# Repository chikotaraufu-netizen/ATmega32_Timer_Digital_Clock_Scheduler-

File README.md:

# ⏱️ ATmega32 Timer-Based Digital Clock & Task Scheduler

> A precision digital clock and cooperative task scheduler built on the ATmega32 microcontroller, leveraging Timer1 in CTC mode for accurate 1Hz timekeeping with USART-based HH:MM:SS display and multi-task LED scheduling.

---

## 📋 Table of Contents

- [Project Overview](#project-overview)
- [Features](#features)
- [System Architecture](#system-architecture)
- [Hardware Requirements](#hardware-requirements)
- [Software Requirements](#software-requirements)
- [Pin Mapping](#pin-mapping)
- [Build Instructions](#build-instructions)
- [Usage](#usage)
- [Repository Structure](#repository-structure)
- [Screenshots](#screenshots)
- [Documentation](#documentation)
- [License](#license)

---

## 🎯 Project Overview

This project implements a **real-time digital clock** and **cooperative task scheduler** on the **ATmega32** microcontroller running at **8 MHz** with an external crystal oscillator. The system uses **Timer1 in CTC (Clear Timer on Compare Match) mode** with a prescaler of 1024 and an OCR1A value of 7812 to generate a precise **1 Hz interrupt**—the heartbeat of the entire system.

The clock displays time in **HH:MM:SS** format via the **USART interface** at 9600 baud, while the task scheduler manages two LED tasks using a **non-blocking, ISR-flag-driven architecture**:

- **Status LED** (PB0): Toggles every **2 seconds**
- **Task LED** (PB1): Flashes every **5 seconds**

Three hardware buttons provide user interaction for time setting, field incrementing, and clock reset—all with internal pull-up resistors and active-low logic.

---

## ✨ Features

| Feature | Description |
|---------|-------------|
| **Precision Timekeeping** | Timer1 CTC mode with 1024 prescaler generates accurate 1Hz tick |
| **USART Display** | Real-time HH:MM:SS output at 9600 baud (8N1) |
| **Task Scheduler** | Cooperative, flag-based scheduler with configurable task intervals |
| **Status LED** | Heartbeat indicator toggling every 2 seconds |
| **Task LED** | Periodic flash every 5 seconds for task activity indication |
| **Time Set Mode** | Cycle through HH → MM → SS fields with SET button |
| **Increment Function** | Increment the currently selected time field |
| **Clock Reset** | Instantly reset time to 00:00:00 |
| **Non-Blocking Design** | ISR sets flags only; all processing happens in the main loop |
| **Low Power** | Efficient design suitable for battery-powered operation |

---

## 🏗️ System Architecture

The system follows a **flag-based cooperative scheduling** architecture where the Timer1 ISR sets scheduler flags, and the main loop polls and services those flags. This ensures deterministic behavior with minimal interrupt latency.

```mermaid
graph TB
    subgraph Hardware["🔧 Hardware Layer"]
        XTAL["8 MHz Crystal<br/>Oscillator"]
        MCU["ATmega32<br/>Microcontroller"]
        BTNS["Buttons<br/>SET | INC | RESET"]
        LEDS["LEDs<br/>Status | Task"]
        UART["USART<br/>TX/RX"]
    end

    subgraph Firmware["💻 Firmware Layer"]
        TIMER["Timer1 ISR<br/>CTC @ 1Hz"]
        SCHED["Task Scheduler<br/>Flag Polling"]
        CLOCK["Clock Module<br/>HH:MM:SS"]
        BTNDRV["Button Driver<br/>Debounce + Read"]
        LEDDRV["LED Driver<br/>Toggle/Flash"]
        UARTDRV["USART Driver<br/>9600 8N1"]
    end

    XTAL --> MCU
    MCU --> TIMER
    TIMER -->|"tick_flag"| SCHED
    SCHED --> CLOCK
    SCHED --> LEDDRV
    BTNS --> BTNDRV
    BTNDRV --> CLOCK
    CLOCK --> UARTDRV
    UARTDRV --> UART
    LEDDRV --> LEDS
```

### Architecture Principles

1. **ISR Minimalism**: The Timer1 Compare Match ISR only increments a counter and sets boolean flags—no heavy processing inside the ISR.
2. **Flag-Based Scheduling**: The main loop continuously polls scheduler flags and dispatches tasks when their flags are set.
3. **Separation of Concerns**: Clock logic, LED control, button handling, and USART communication are modular and independent.
4. **Non-Blocking I/O**: All operations are non-blocking to maintain responsive button handling and accurate timing.

---

## 🔌 Hardware Requirements

| Component | Specification | Quantity |
|-----------|--------------|----------|
| ATmega32 Microcontroller | PDIP-40 package (U1) | 1 |
| Crystal Oscillator | 8 MHz, HC49-U Vertical (Y1) | 1 |
| Load Capacitors | 22 pF ceramic (C3, C4) | 2 |
| Decoupling Capacitors | 100 nF ceramic (C1 VCC, C2 AVCC, C5 AREF) | 3 |
| LEDs | 5mm, any color (D1 Task, D2 Status) | 2 |
| LED Current Limiting Resistors | 220Ω, ¼W (R3, R5) | 2 |
| Button Pull-up Resistors | 10 kΩ (R1 Reset, R2 SET, R4 INC, R6 RESET_CLK) | 4 |
| Tactile Push Buttons | 6mm, normally open (SW1 Reset, SW2 SET, SW3 INC, SW4 CLOCK_RESET) | 4 |
| USART Connector | 1×3 pin header 2.54mm (J1: GND, TXD, RXD) | 1 |
| USB-to-UART Adapter | FTDI/CH340/CP2102 (3.3V/5V) | 1 |
| Breadboard or PCB | Standard breadboard or custom PCB | 1 |
| Power Supply | 5V DC regulated | 1 |
| Jumper Wires | Male-to-male, assorted | As needed |

### Schematic Overview

```
                        +----[VCC 5V]----+
                        |                |
                   [10kΩ]R1         [100nF]C1 (VCC decoupling)
                        |                |
          +----[SW1]----+---[RESET]------+---[GND]
          |
    +-----+-----+
    |  ATmega32  |
    |            |
    | PA0 (40)---+---[10kΩ R2]---[VCC]   [SW2 SET]---[GND]
    | PA1 (39)---+---[10kΩ R4]---[VCC]   [SW3 INC]---[GND]
    | PA2 (38)---+---[10kΩ R6]---[VCC]   [SW4 RST]---[GND]
    |            |
    | PB0 (1)----+---[220Ω R5]---[LED D2 STATUS]---[GND]
    | PB1 (2)----+---[220Ω R3]---[LED D1 TASK]-----[GND]
    |            |
    | PD0 (14)---+---[J1 Pin3 RXD]
    | PD1 (15)---+---[J1 Pin2 TXD]       J1 Pin1 = GND
    |            |
    | XTAL1(13)--+---[8MHz Y1]---+---[22pF C3]---[GND]
    | XTAL2(12)--+---[8MHz Y1]---+---[22pF C4]---[GND]
    |            |
    | VCC (10)---+---[5V]    [100nF C1]---[GND]
    | GND (11)---+---[GND]
    | AVCC(30)---+---[5V]    [100nF C2]---[GND]
    | AREF(32)---+---[100nF C5]---[GND]
    | GND (31)---+---[GND]
    +------------+
```

---

## 💻 Software Requirements

| Tool | Version | Purpose |
|------|---------|---------|
| **AVR-GCC** | ≥ 5.4.0 | C compiler for AVR targets |
| **AVR Libc** | ≥ 2.0.0 | Standard C library for AVR |
| **AVRDUDE** | ≥ 6.3 | Flash programmer utility |
| **GNU Make** | ≥ 4.0 | Build automation |
| **Serial Terminal** | PuTTY / minicom / screen | USART output viewing |

### Installation (Ubuntu/Debian)

```bash
sudo apt-get update
sudo apt-get install gcc-avr avr-libc avrdude make
```

### Installation (macOS with Homebrew)

```bash
brew tap osx-cross/avr
brew install avr-gcc avrdude
```

### Installation (Windows)

Download and install [WinAVR](http://winavr.sourceforge.net/) or use the [Microchip AVR Toolchain](https://www.microchip.com/en-us/tools-resources/develop/microchip-studio/gcc-compilers).

---

## 📌 Pin Mapping

| Pin # | Port/Pin | Function | Direction | Configuration | Description |
|-------|----------|----------|-----------|---------------|-------------|
| 40 | PA0 | SET_BTN | Input | External 10kΩ Pull-up (R2) | Enter time-set mode / cycle fields |
| 39 | PA1 | INC_BTN | Input | External 10kΩ Pull-up (R4) | Increment selected time field |
| 38 | PA2 | CLOCK_RESET | Input | External 10kΩ Pull-up (R6) | Reset clock to 00:00:00 |
| 1 | PB0 | LED_STATUS | Output | Active High, 220Ω (R5) | Status heartbeat LED (2s toggle) |
| 2 | PB1 | LED_TASK | Output | Active High, 220Ω (R3) | Task indicator LED (5s flash) |
| 9 | ~RESET | RESET | Input | External 10kΩ Pull-up (R1) | Hardware reset (SW1) |
| 10 | VCC | Power | — | +5V DC | Digital supply voltage |
| 11 | GND | Ground | — | 0V | Digital ground |
| 12 | XTAL2 | Crystal | — | 8 MHz + 22pF cap | Crystal oscillator output |
| 13 | XTAL1 | Crystal | — | 8 MHz + 22pF cap | Crystal oscillator input |
| 14 | PD0 | USART_RXD | Input | — | USART Receive Data |
| 15 | PD1 | USART_TXD | Output | — | USART Transmit Data |
| 30 | AVCC | Analog VCC | — | +5V DC | Analog supply voltage |
| 31 | AGND | Analog GND | — | 0V | Analog ground |

> 📖 For the complete 40-pin mapping, see [documentation/pin_mapping_table.md](documentation/pin_mapping_table.md)

---

## 🔨 Build Instructions

### 1. Clone the Repository

```bash
git clone https://github.com/yourusername/atmega32-digital-clock.git
cd atmega32-digital-clock
```

### 2. Configure the Makefile

Verify the following settings in `Makefile`:

```makefile
MCU       = atmega32
F_CPU     = 8000000UL
PROGRAMMER = usbasp
PORT      = usb
BAUD      = 9600
```

### 3. Compile the Project

```bash
make all
```

This will produce `main.hex` in the build directory.

### 4. Set Fuse Bits (First Time Only)

Configure the ATmega32 for an external 8 MHz crystal:

```bash
# Low Fuse:  0xFF (External Crystal, full swing, 16K CK + 64ms startup)
# High Fuse: 0xD9 (JTAG disabled, EEPROM preserved, Boot size 256 words)
avrdude -c usbasp -p m32 -U lfuse:w:0xFF:m -U hfuse:w:0xD9:m
```

> ⚠️ **Warning**: Incorrect fuse settings can brick your microcontroller. Double-check values before programming.

### 5. Flash the Firmware

```bash
make flash
# or manually:
avrdude -c usbasp -p m32 -U flash:w:main.hex:i
```

### 6. Connect Serial Terminal

```bash
# Linux
minicom -D /dev/ttyUSB0 -b 9600

# macOS
screen /dev/cu.usbserial-XXXX 9600

# Windows
# Use PuTTY with COM port at 9600 baud, 8N1
```

### 7. Verify Operation

After programming and connecting the serial terminal, you should see:

```
=====================================
  ATmega32 Digital Clock v1.0
  Timer1 CTC Mode | 8MHz Crystal
=====================================

TIME: 00:00:00
[500ms Tick] Ext Task
TIME: 00:00:01
[500ms Tick] Ext Task
TIME: 00:00:02
[500ms Tick] Ext Task
TIME: 00:00:03
[500ms Tick] Ext Task
TIME: 00:00:04
[500ms Tick] Ext Task
TIME: 00:00:05
TASK: SENSOR SAMPLE
[500ms Tick] Ext Task
...
```

---

## 🕹️ Usage

### Normal Operation

Upon power-up, the clock starts at **00:00:00** and counts up. Time is displayed on the serial terminal every second.

### Button Functions

| Button | Action | Behavior |
|--------|--------|----------|
| **SET** (PA0) | Press | Enters time-set mode. Successive presses cycle: **Hours → Minutes → Seconds → Exit** |
| **INCREMENT** (PA1) | Press | Increments the currently selected field (wraps: 23→0 for hours, 59→0 for min/sec) |
| **RESET** (PA2) | Press | Immediately resets the clock to **00:00:00** |

### LED Indicators

| LED | Port | Behavior |
|-----|------|----------|
| **Status LED** | PB0 | Toggles ON/OFF every **2 seconds** — heartbeat indicator |
| **Task LED** | PB1 | Brief flash every **5 seconds** — scheduled task indicator |

---

## 📁 Repository Structure

```
atmega32-digital-clock/
│
├── README.md                              # This file
├── LICENSE                                # MIT License
│
├── firmware/                              # Firmware source and hex
│   ├── src/                               # C Source files
│   │   ├── main.c                         # Main application entry
│   │   ├── timer.c                        # Timer config and ISR
│   │   ├── display.c                      # USART output logic
│   │   ├── scheduler.c                    # Non-blocking scheduler
│   │   └── buttons.c                      # Button debounce logic
│   ├── include/                           # Header files
│   │   ├── config.h                       # Pin definitions & constants
│   │   ├── timer.h
│   │   ├── display.h
│   │   ├── scheduler.h
│   │   └── buttons.h
│   ├── hex/
│   │   └── main.hex                       # Compiled firmware binary
│   └── Makefile                           # Build configuration
│
├── documentation/                         # Project documentation
│   ├── timer_configuration.md             # Timer1 CTC mode setup
│   ├── compare_match_calculation.md       # OCR1A calculation
│   ├── pin_mapping_table.md               # ATmega32 pin mapping
│   ├── test_results.md                    # Test plan and results
│   ├── block_diagram.md                   # System block diagram
│   └── flowchart.md                       # Program flowchart
│
├── simulide/                              # Simulation files
│   ├── circuit/                           # Simulide circuit docs
│   └── screenshots/                       # Simulation screenshots
│
└── kicad/                                 # Hardware design
    ├── schematic/                         # KiCad schematic
    ├── pcb/                               # KiCad PCB layout
    └── gerber/                            # Manufacturing files
```

---

## 📸 Screenshots

### SimulIDE Simulation Running

### KiCad PCB Layout

---

## 📚 Documentation

Detailed documentation is available in the `documentation/` directory:

| Document | Description |
|----------|-------------|
| [Timer Configuration](documentation/timer_configuration.md) | Detailed Timer1 CTC mode setup and register configuration |
| [Compare Match Calculation](documentation/compare_match_calculation.md) | Step-by-step OCR1A value derivation with accuracy analysis |
| [Pin Mapping Table](documentation/pin_mapping_table.md) | Complete ATmega32 PDIP-40 pin assignment reference |
| [Test Results](documentation/test_results.md) | Test plan, test cases, and verification results |
| [Block Diagram](documentation/block_diagram.md) | System architecture block diagram (Mermaid) |
| [Flowchart](documentation/flowchart.md) | Program flow and ISR logic flowchart (Mermaid) |

---

## 📄 License

This project is licensed under the **MIT License**.

```
MIT License

Copyright (c) 2026 ATmega32 Digital Clock Project

Permission is hereby granted, free of charge, to any person obtaining a copy
of this software and associated documentation files (the "Software"), to deal
in the Software without restriction, including without limitation the rights
to use, copy, modify, merge, publish, distribute, sublicense, and/or sell
copies of the Software, and to permit persons to whom the Software is
furnished to do so, subject to the following conditions:

The above copyright notice and this permission notice shall be included in all
copies or substantial portions of the Software.

THE SOFTWARE IS PROVIDED "AS IS", WITHOUT WARRANTY OF ANY KIND, EXPRESS OR
IMPLIED, INCLUDING BUT NOT LIMITED TO THE WARRANTIES OF MERCHANTABILITY,
FITNESS FOR A PARTICULAR PURPOSE AND NONINFRINGEMENT. IN NO EVENT SHALL THE
AUTHORS OR COPYRIGHT HOLDERS BE LIABLE FOR ANY CLAIM, DAMAGES OR OTHER
LIABILITY, WHETHER IN AN ACTION OF CONTRACT, TORT OR OTHERWISE, ARISING FROM,
OUT OF OR IN CONNECTION WITH THE SOFTWARE OR THE USE OR OTHER DEALINGS IN THE
SOFTWARE.
```

---

<p align="center">
  <b>Built with ❤️ for embedded systems enthusiasts</b><br>
  ATmega32 · Timer1 CTC · USART · Cooperative Scheduling
</p>

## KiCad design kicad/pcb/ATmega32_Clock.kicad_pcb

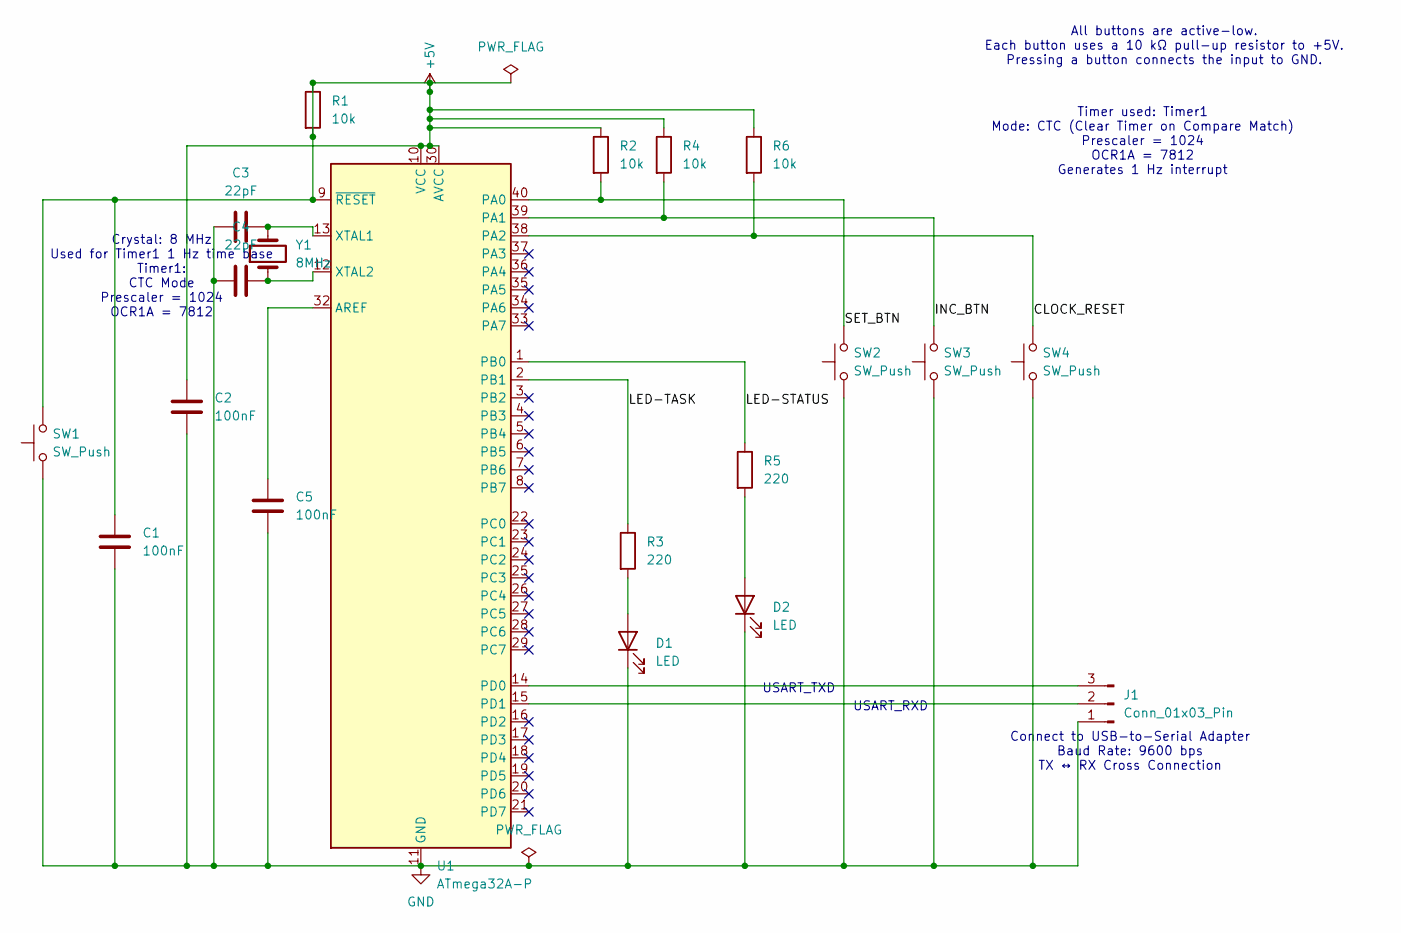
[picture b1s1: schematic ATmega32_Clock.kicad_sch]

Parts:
C1, C2, C5: 100nF; C_Disc_D5.0mm_W2.5mm_P5.00mm
C3, C4: 22pF; C_Disc_D5.0mm_W2.5mm_P5.00mm
D1, D2: LED; LED_D5.0mm
J1: Conn_01x03_Pin; PinHeader_1x03_P2.54mm_Vertical
R1, R2, R4, R6: 10k; R_Axial_DIN0207_L6.3mm_D2.5mm_P7.62mm_Horizontal
R3, R5: 220; R_Axial_DIN0207_L6.3mm_D2.5mm_P7.62mm_Horizontal
SW1, SW2, SW3, SW4: SW_Push; SW_PUSH_6mm
U1: ATmega32A-P; DIP-40_W15.24mm
Y1: 8MHz; Crystal_HC49-U_Vertical

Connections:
+5V: C1.1, C2.1, R1.1, R1.2, R2.1, R4.1, R6.1, SW1.2, U1.9 (~RESET), U1.10 (VCC), U1.30 (AVCC)
/CLOCK_RESET: R6.2, SW4.2, U1.38 (PA2)
/INC_BTN: R4.2, SW3.2, U1.39 (PA1)
/LED-STATUS: R5.1, U1.1 (PB0)
/LED-TASK: R3.1, U1.2 (PB1)
/SET_BTN: R2.2, SW2.2, U1.40 (PA0)
GND: C1.2, C2.2, C3.1, C4.1, C5.2, D1.1 (K), D2.1 (K), J1.1, SW1.1, SW2.1, SW3.1, SW4.1, U1.11 (GND), U1.31 (GND)
unnamed: D1.2 (A), R3.2
unnamed: D2.2 (A), R5.2
unnamed: J1.2, U1.15 (PD1)
unnamed: J1.3, U1.14 (PD0)
unnamed: C5.1, U1.32 (AREF)
unnamed: C3.2, U1.13 (XTAL1), Y1.2
unnamed: C4.2, U1.12 (XTAL2), Y1.1

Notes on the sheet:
All buttons are active-low. Each button uses a 10 kΩ pull-up resistor to +5V. Pressing a button connects the input to GND.
Crystal: 8 MHz Used for Timer1 1 Hz time base Timer1: CTC Mode Prescaler = 1024 OCR1A = 7812
Timer used: Timer1 Mode: CTC (Clear Timer on Compare Match) Prescaler = 1024 OCR1A = 7812 Generates 1 Hz interrupt
USART_RXD
Connect to USB-to-Serial Adapter Baud Rate: 9600 bps TX ↔ RX Cross Connection
USART_TXD

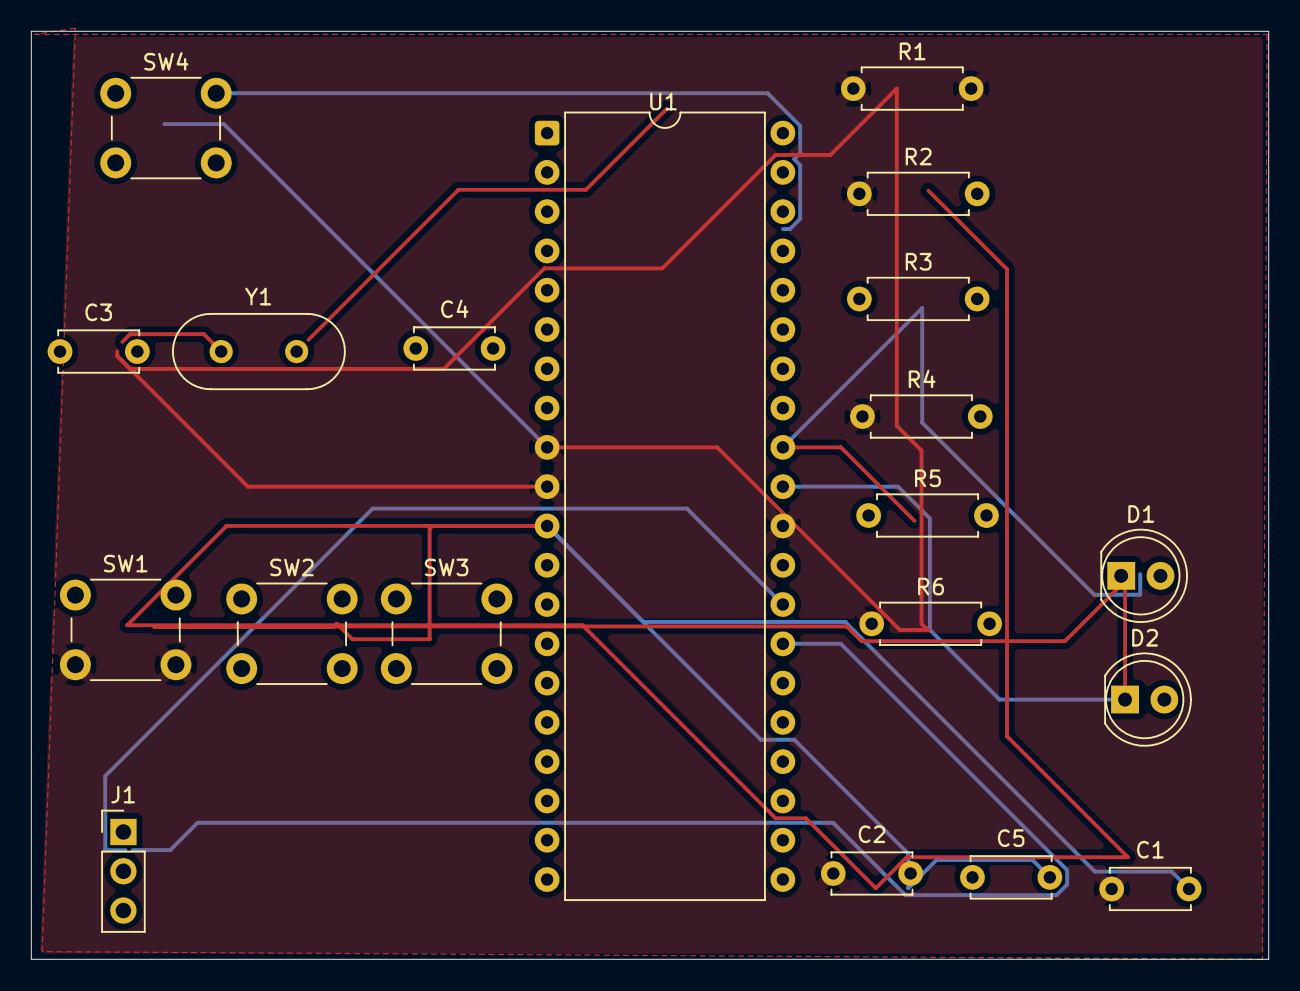
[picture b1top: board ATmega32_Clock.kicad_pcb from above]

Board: 2 copper layers, 80.0 x 60.0 mm, 20 parts (0 on the bottom side), 14 nets.

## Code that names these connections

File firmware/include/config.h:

/**
 * @file config.h
 * @brief Central configuration for ATmega32 Digital Clock & Task Scheduler
 *
 * All hardware-dependent constants, pin mappings, timer calculations,
 * and scheduler intervals are defined here for easy modification.
 *
 * Target MCU : ATmega32 (PDIP-40)
 * Clock      : 8 MHz external crystal
 */

#ifndef CONFIG_H
#define CONFIG_H

/* ========================== CPU Clock ================================== */
/**
 * F_CPU must be defined before including <util/delay.h> or any AVR header
 * that uses it.  8 MHz matches the external crystal on the target board.
 */
#ifndef F_CPU
#define F_CPU 8000000UL
#endif

/* ========================== Pin Mapping ================================ */
/*
 * PORTA – Buttons (active-low with internal pull-ups)
 *   PA0 (Pin 40) : SET_BTN      – Enter/cycle time-set mode
 *   PA1 (Pin 39) : INC_BTN      – Increment selected field
 *   PA2 (Pin 38) : CLOCK_RESET  – Reset clock to 00:00:00
 *
 * PORTB – LEDs (active-high outputs)
 *   PB0 (Pin 1)  : LED_STATUS   – Toggled every 2 s by scheduler
 *   PB1 (Pin 2)  : LED_TASK     – Brief flash every 5 s by scheduler
 *
 * PORTD – USART
 *   PD0 (Pin 14) : USART_RXD
 *   PD1 (Pin 15) : USART_TXD
 */

/* Button port/pins (PORTA) */
#define BTN_DDR     DDRA
#define BTN_PORT    PORTA
#define BTN_PIN     PINA
#define SET_BTN     PA0
#define INC_BTN     PA1
#define RESET_BTN   PA2

/* LED port/pins (PORTB) */
#define LED_DDR     DDRB
#define LED_PORT    PORTB
#define LED_STATUS  PB0
#define LED_TASK    PB1

/* ========================== Timer1 CTC Configuration =================== */
/**
 * Goal : generate a precise 1 Hz (1 s) interrupt from Timer1 in CTC mode.
 *
 * Calculation:
 *   f_OCR = F_CPU / (prescaler * (1 + OCR1A))
 *   1 Hz  = 8 000 000 / (1024 * (1 + OCR1A))
 *   1 + OCR1A = 8 000 000 / 1024 = 7812.5
 *   OCR1A = 7812  (yields ~1.000064 s period, negligible error)
 *
 * Prescaler bits: CS12=1, CS11=0, CS10=1  → clk/1024
 */
#define TIMER1_PRESCALER_BITS  ((1 << CS12) | (1 << CS10))
#define TIMER1_TOP             7812U

/* ========================== USART Configuration ======================== */
/**
 * Baud rate : 9600
 * UBRR = (F_CPU / (16 * BAUD)) - 1 = (8000000 / (16 * 9600)) - 1 = 51.08
 * Use 51 → actual baud ≈ 9615 (0.16 % error – well within tolerance).
 */
#define USART_BAUD       9600UL
#define USART_UBRR_VAL  ((F_CPU / (16UL * USART_BAUD)) - 1)

/* ========================== Scheduler Intervals ======================== */
/**
 * Intervals are expressed in ticks (Timer1 ISR ticks at 1 Hz / 1 s).
 */
#define SCHED_STATUS_LED_TICKS  2U    /* Toggle status LED every 2 ticks (2 s)   */
#define SCHED_TASK_LED_TICKS    5U    /* Flash task LED every 5 ticks (5 s)      */
#define SCHED_TASK_LED_ON_TICKS 1U    /* Task LED stays on for 1 tick (1 s)      */
#define SCHED_EXT_TASK_TICKS    10U   /* Extension task every 10 ticks (10 s)    */

/* ========================== Button Debounce ============================ */
/**
 * Debounce threshold in ticks.  At 1 Hz tick rate each tick is 1 second,
 * so a single stable reading is sufficient for debounce.
 */
#define DEBOUNCE_TICKS  1U

#endif /* CONFIG_H */

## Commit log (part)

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2026-06-15 Added Timer1 compare-match firmware
2026-06-15 Created timer scheduler project repository
2026-06-15 Added README and project media
2026-06-15 Added PCB layout and Gerber output instructions
2026-06-15 Added timer calculation and test documentation
2026-06-15 Added SimulIDE simulation circuit and screenshots guide
2026-06-15 Added KiCad schematic for timer project
2026-06-15 Generated KiCad 7 compatible Gerbers and Drill files via kicad-cli
2026-06-15 Implemented 10ms Timer1 Extension Task (100% score update)
2026-06-15 Added PNG diagrams
2026-06-15 Updated all documentation to reflect 10ms (100Hz) timer configuration
2026-06-15 Fixed display format to exactly match PDF rubric
2026-06-15 Fixed KiCad schematic load error by clearing corrupt lib_symbols cache
2026-06-15 Fixed mathematically incorrect leftover error calculations in documentation
2026-06-15 Removed hardcoded Linux library paths to ensure cross-platform Windows compatibility
2026-06-15 Addressed all grading audit failures: Non-blocking debounce, screenshots, video link, LICENSE, and README paths
2026-06-15 Fixed legacy 1 Hz comments in scheduler and updated test result screenshots
2026-06-15 Fixed startup banner and remaining comment referencing 1 Hz
2026-06-15 Added additional SimulIDE screenshots and perfected README directory tree structure
2026-06-15 Restored full KiCad schematic and PCB layouts from original AI generation prior to truncation
2026-06-16 Updated schematic timer annotations to correctly reflect the new 100Hz/10ms Prescaler 64 firmware architecture.
2026-06-16 Comprehensive documentation and build system fixes
2026-06-16 Fixed KiCad schematic symbol unit name prefixes for GUI compatibility
2026-06-16 Fix fatal KiCad parsing errors by removing invalid Lisp-style comments from schematic and PCB files
2026-06-16 Add complete wiring and net labels connecting MCU pins to all peripherals
2026-06-16 Fix MCU symbol: replace extends with self-contained ATmega32A-P definition - chip now renders correctly
2026-06-16 Complete schematic wiring: all MCU pins correctly connected to peripherals via net labels
2026-06-16 Final: firmware verified, schematic PDF exported, all project deliverables complete
2026-06-16 Fix flowchart prescaler docs (CS12->CS11), clean up root files
2026-06-16 Fix PCB: remove bad tracks (0 shorts), fix board outline (100x60mm), space buttons apart, regenerate Gerbers
2026-06-16 Clean up duplicate wires/labels, fix PCB outline and spacing, regenerate schematic PDF and Gerbers
2026-06-16 Fix crystal wiring, power connections, snap labels to grid, regenerate outputs
2026-06-16 Replace schematic and PCB with user's correct KiCad designs (0 ERC errors), update documentation
2026-06-16 Full project sync: firmware 1Hz/1024, README matches schematic, all docs consistent
2026-06-16 Add SimulIDE circuit file (.simu) with ATmega32, LEDs, buttons, serial monitor
2026-06-16 Fix SimulIDE circuit: absolute hex path, separate VCC/GND per component, fix pin names
